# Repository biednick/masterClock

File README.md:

# Master Clock

## Features
This module features tap tempo, 1x, 2x, 3x, 4x, 1/2x, 1/3x, and 1/4x clock multiplication/division, and the ability to dial in the clock rate using a potentiometer. A second mode disables tap tempo and allows rate to be adjusted directly using the potentiometer or allows the module to be used as a standard clock mutiplier/divider..

## Files
### Master_Clock_xx.ino
This is the Arduino code. An ISP header on the board allows the microcontroller to be programmed directly.

### masterClock_xx.brd and .sch
These are the Eagle files for the PCB. To order PCBs, gerbers need to be generated using a CAM job in Eagle. A free version of Eagle is available.

### masterClockParts_xx.md
This is the parts list. A Mouser BOM is available at in this file as well.

### masterClock.ai
This is the panel in Adobe Illustrator format. This can be used to manufacture a panel.

## Updates

### 01.1 03JAN19
The original code had major issues with timing. That code has been replaced with a test version of the code that keeps time correctly but only allows the tempo to be set using the potentiometer. All pin deffinitions were left in place to facilitate adding additonal code to meet the desired funsitonality. In additon, I have discovered the anode on LD1 (the bicolor LED) is not connected to VCC. This can be fixed with a jumper wire and will be corrected in the next board revition. 

### 01 24JUN18
First push to GitHub. Currently this design is untested.

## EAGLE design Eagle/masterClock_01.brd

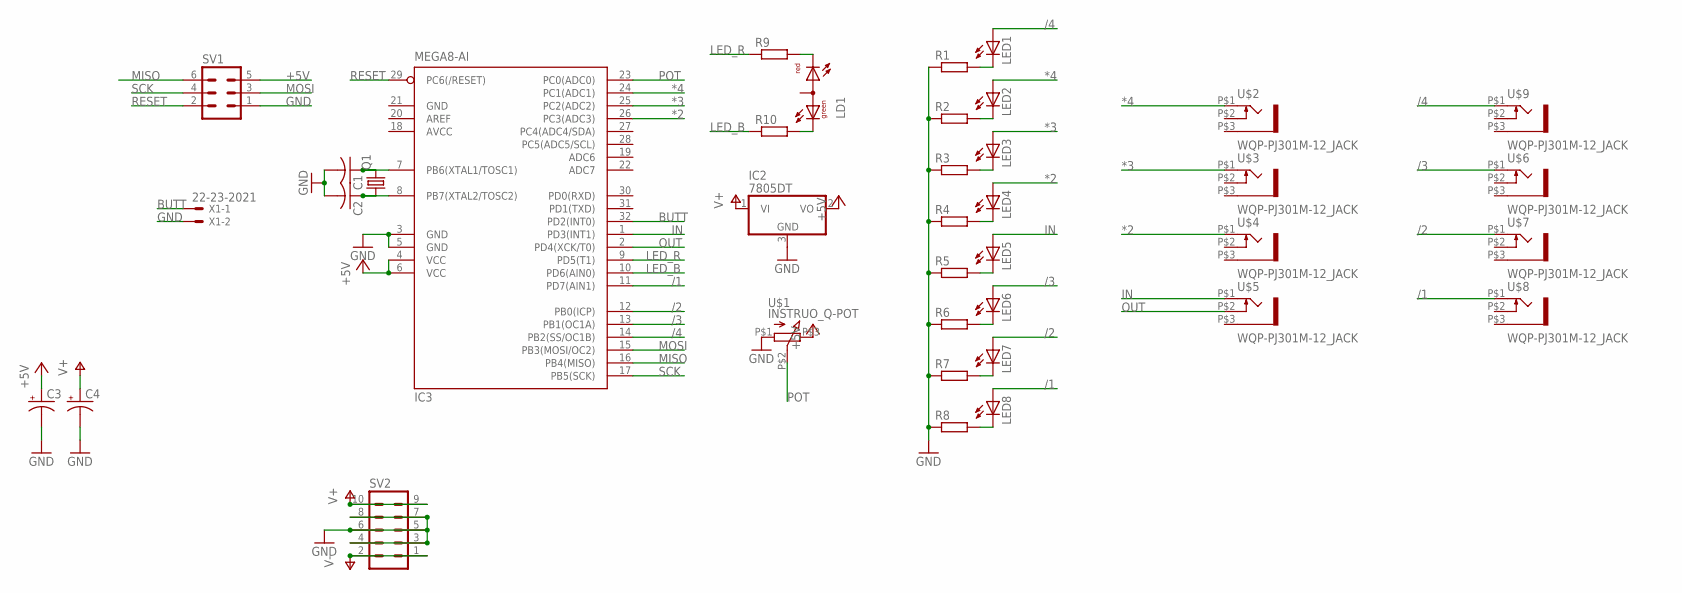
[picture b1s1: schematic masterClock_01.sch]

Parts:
C1, C2: C-USC0805; C0805
C3, C4: CPOL-US153CLV-0505; 153CLV-0505
IC2: 7805DT; TO252
IC3: MEGA8-AI; TQFP32-08
LD1: DUOLED-RG-A; DUOLED-A-5MM
LED1, LED2, LED3, LED4, LED5, LED6, LED7, LED8: LED5MM
Q1: CRYSTALHC49UP; HC49UP
R1, R2, R3, R4, R5, R6, R7, R8, R9, R10: R; R0805
SV1: MA03-2
SV2: MA05-2
U$1: INSTRUO_Q-POT
U$2, U$3, U$4, U$5, U$6, U$7, U$8, U$9: WQP-PJ301M-12_JACK
X1: 22-23-2021

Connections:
*2: IC3.26 (PC3(ADC3)), LED4.A, U$4.P$1 (2)
*3: IC3.25 (PC2(ADC2)), LED3.A, U$3.P$1 (2)
*4: IC3.24 (PC1(ADC1)), LED2.A, U$2.P$1 (2)
+5V: C3.+, IC2.2 (VO), IC3.4 (VCC), IC3.6 (VCC), SV1.5, U$1.P$3 (3)
/1: IC3.11 (PD7(AIN1)), LED8.A, U$8.P$1 (2)
/2: IC3.12 (PB0(ICP)), LED7.A, U$7.P$1 (2)
/3: IC3.13 (PB1(OC1A)), LED6.A, U$6.P$1 (2)
/4: IC3.14 (PB2(SS/OC1B)), LED1.A, U$9.P$1 (2)
AVCC: IC3.18 (AVCC)
BUTT: IC3.32 (PD2(INT0)), X1.1
GND: C1.2, C2.2, C3.-, C4.-, IC2.3 (GND), IC3.3 (GND), IC3.5 (GND), IC3.21 (GND), R1.1, R2.1, R3.1, R4.1, R5.1, R6.1, R7.1, R8.1, SV1.1, SV2.3, SV2.4, SV2.5, SV2.6, SV2.7, SV2.8, U$1.P$1 (1), X1.2
IN: IC3.1 (PD3(INT1)), LED5.A, U$5.P$1 (2)
LED_B: IC3.10 (PD6(AIN0)), R10.1
LED_R: IC3.9 (PD5(T1)), R9.1
MISO: IC3.16 (PB4(MISO)), SV1.6
MOSI: IC3.15 (PB3(MOSI/OC2)), SV1.3
unnamed: LED1.K (C), R1.2
unnamed: LED2.K (C), R2.2
unnamed: LED3.K (C), R3.2
unnamed: LED4.K (C), R4.2
unnamed: LED5.K (C), R5.2
unnamed: LED6.K (C), R6.2
unnamed: LED7.K (C), R7.2
unnamed: LED8.K (C), R8.2
unnamed: LD1.CR, R9.2
unnamed: LD1.CX (CG), R10.2
unnamed: C1.1, IC3.7 (PB6(XTAL1/TOSC1)), Q1.2
unnamed: C2.1, IC3.8 (PB7(XTAL2/TOSC2)), Q1.1
OUT: IC3.2 (PD4(XCK/T0)), U$5.P$2 (3)
POT: IC3.23 (PC0(ADC0)), U$1.P$2 (2)
RESET: IC3.29 (PC6(/RESET)), SV1.2
SCK: IC3.17 (PB5(SCK)), SV1.4
V+: C4.+, IC2.1 (VI), SV2.9, SV2.10
V-: SV2.1, SV2.2

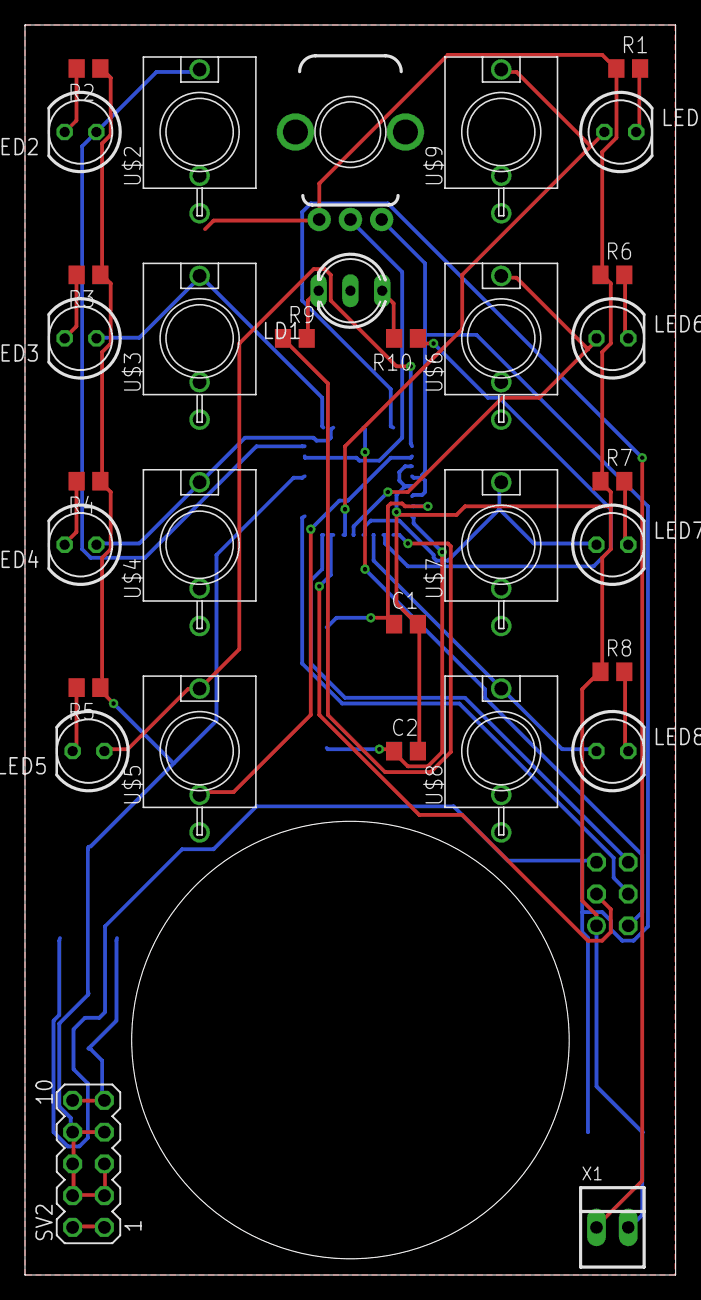
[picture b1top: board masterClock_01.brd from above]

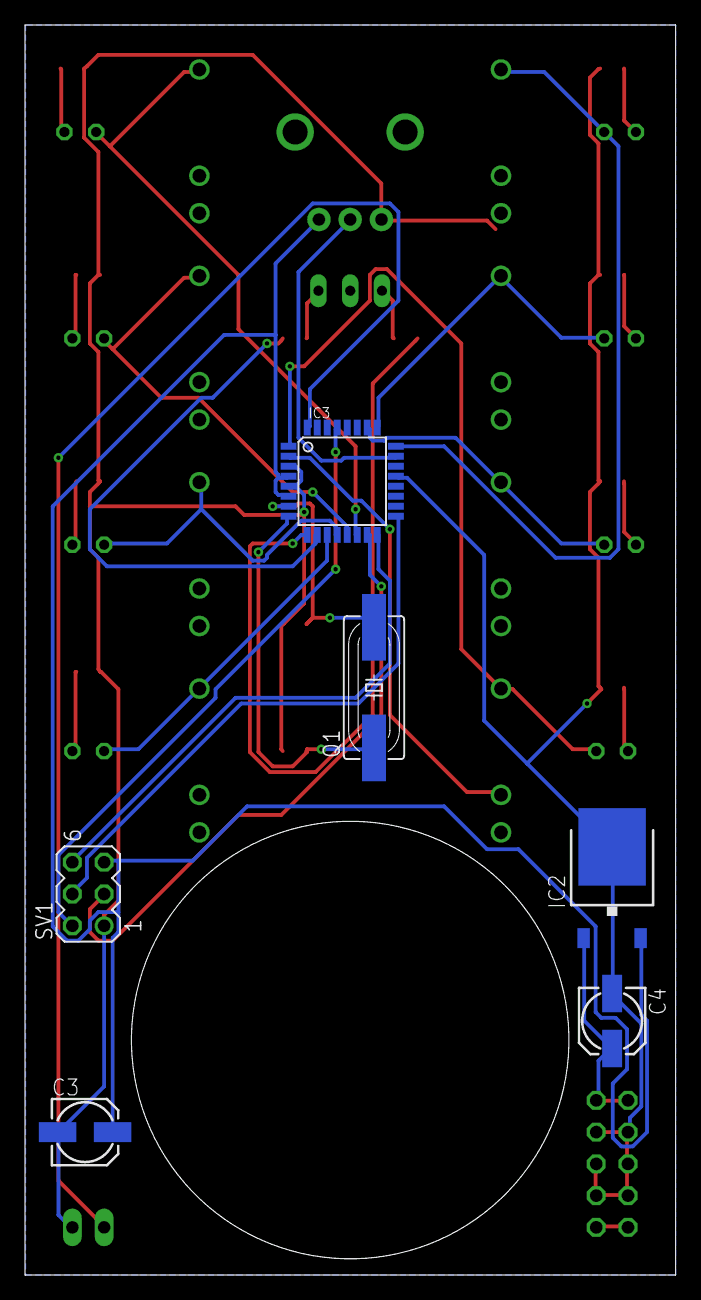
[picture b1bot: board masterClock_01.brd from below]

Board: 2 copper layers, 52.0 x 100.0 mm, 38 parts (6 on the bottom side), 33 nets.

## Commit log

2018-07-24 Format
2018-07-24 Update BOM
2018-07-24 Update File Names
2018-07-25 Set theme jekyll-theme-minimal
2018-07-25 Add Docs folder
2018-07-25 Remove Docs
2018-07-25 Pages
2018-07-25 Update Pages
2018-07-26 Site Update
2018-07-31 Fix mouser BOM, update site
2018-07-31 Add License
2018-08-22 Add Panel
2019-01-04 Uploaded test code. Update README
